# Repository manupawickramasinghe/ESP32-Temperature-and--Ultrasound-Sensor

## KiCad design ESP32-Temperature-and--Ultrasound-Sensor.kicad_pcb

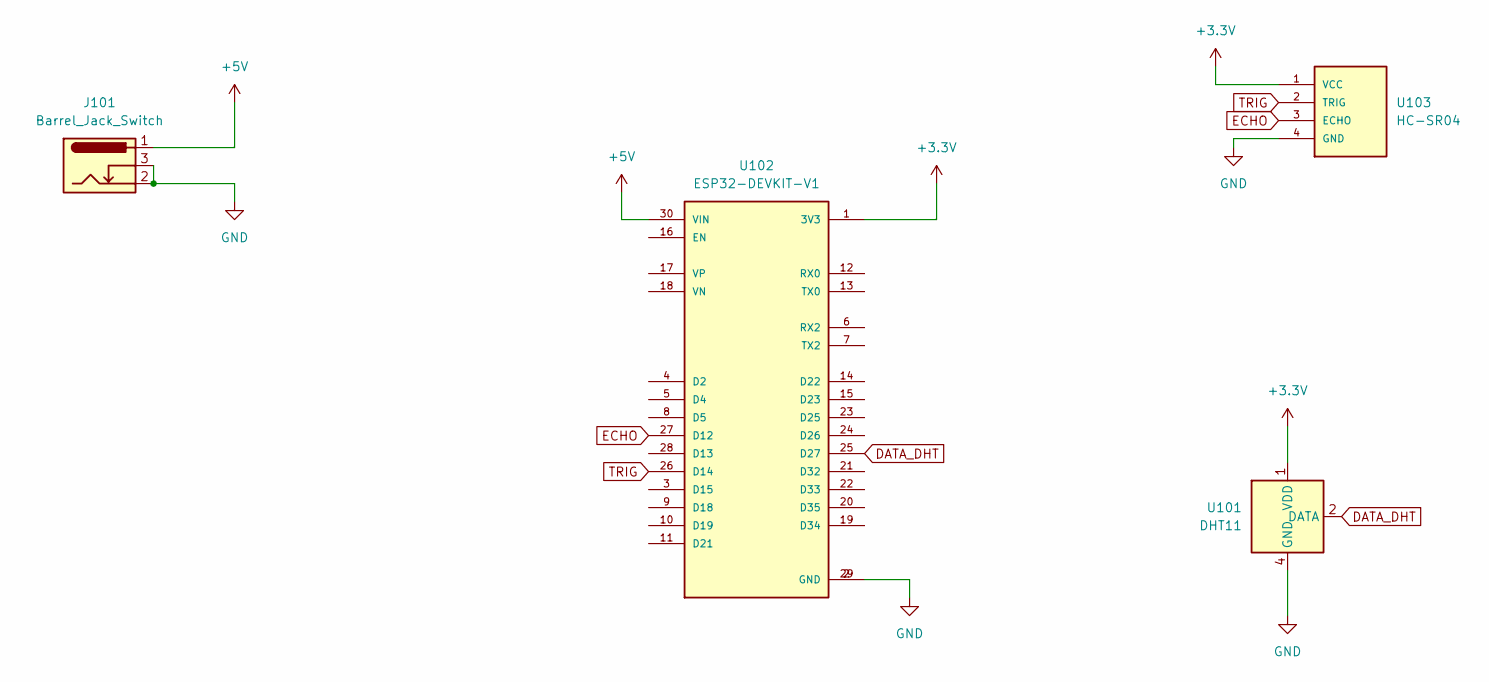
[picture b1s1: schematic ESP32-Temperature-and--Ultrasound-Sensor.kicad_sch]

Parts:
J101: Barrel_Jack_Switch; BarrelJack_Horizontal
U101: DHT11; Aosong_DHT11_5.5x12.0_P2.54mm
U102: ESP32-DEVKIT-V1; MODULE_ESP32_DEVKIT_V1; PARTREV N/A
U103: HC-SR04; XCVR_HC-SR04

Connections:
+3.3V: U101.1 (VDD), U102.1 (3V3), U103.1 (VCC)
+5V: J101.1, U102.30 (VIN)
DATA_DHT: U101.2 (DATA), U102.25 (D27)
ECHO: U102.27 (D12), U103.3 (ECHO)
GND: J101.2, J101.3, U101.4 (GND), U102.2 (GND), U102.29 (GND), U103.4 (GND)
TRIG: U102.26 (D14), U103.2 (TRIG)

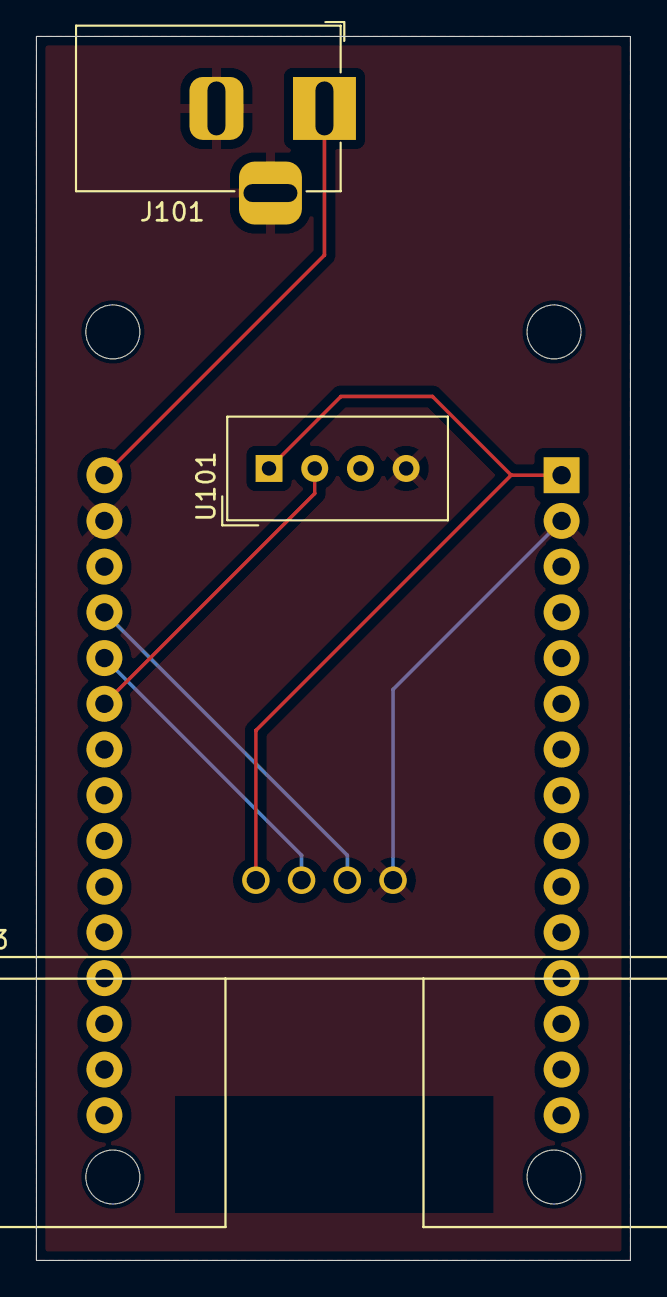
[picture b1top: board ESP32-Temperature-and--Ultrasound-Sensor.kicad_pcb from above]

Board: 2 copper layers, 33.0 x 68.0 mm, 4 parts (1 on the bottom side), 6 nets.

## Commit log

2024-05-29 Final Commit
